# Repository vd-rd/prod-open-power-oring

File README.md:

# PowerPath controller with HotSwap protection

This module is designed to provide redundant power supply for power rails between 5-36V. Depending on the components that are populated on the board it can deliver up to 40A of current. The module can be used in a standalone configuration (switches are provided to select desired functionality) or can be controlled using the 2.54 pin header.

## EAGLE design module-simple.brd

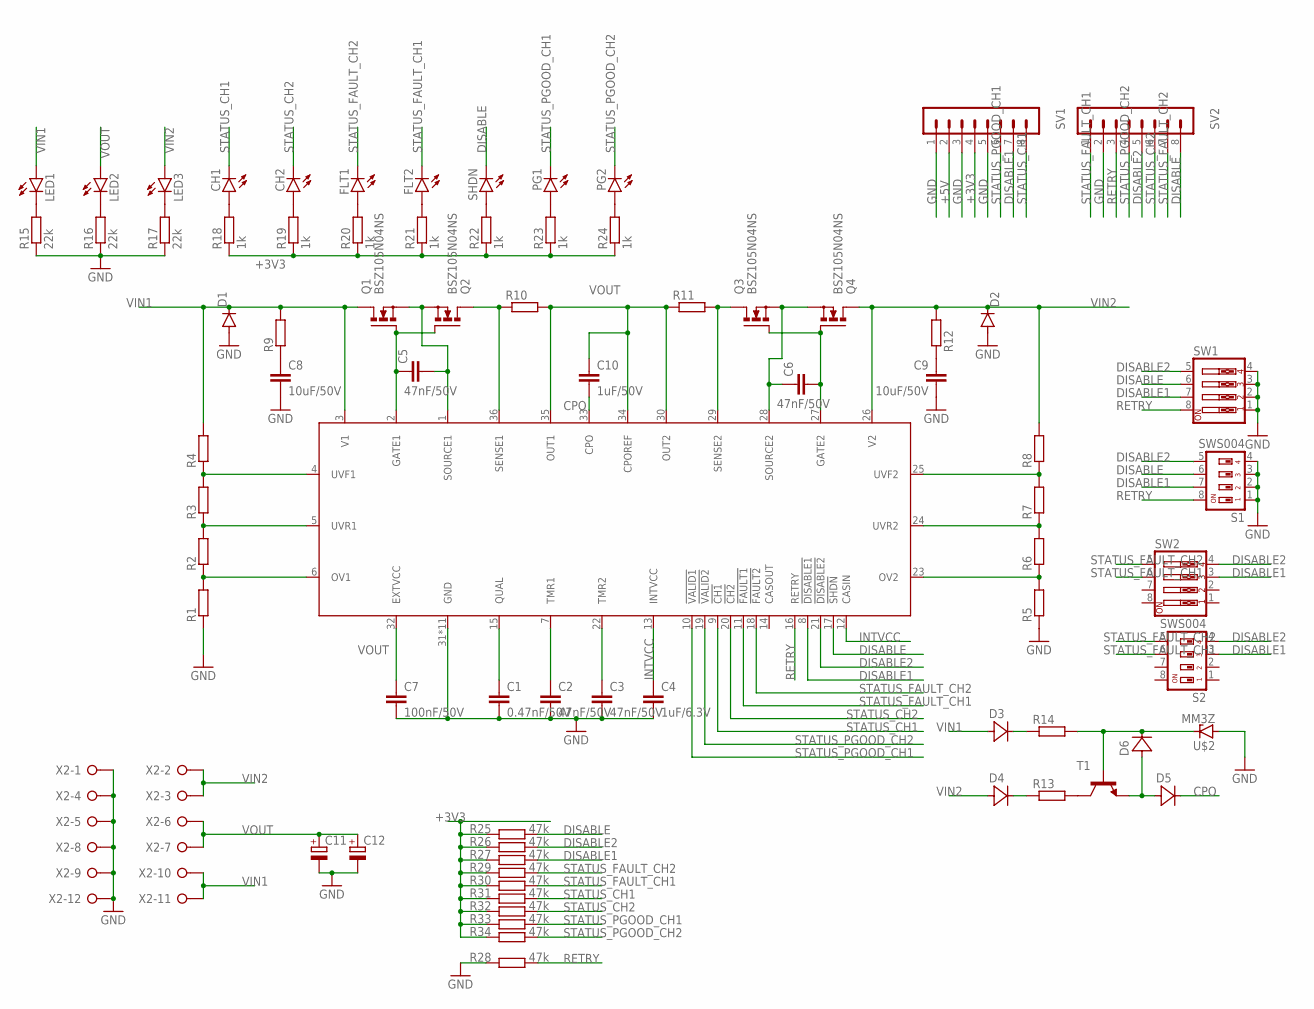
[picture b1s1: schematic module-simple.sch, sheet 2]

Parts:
C1: 0.47nF/50V; C0603
C2, C3, C5, C6: 47nF/50V; C0603
C4: 1uF/6.3V; C0603
C7: 100nF/50V; C0603
C8, C9: 10uF/50V; C1206
C10: 1uF/50V; C0805
C11, C12: CPOL-EU140CLH-1010; 140CLH-1010
CH1, CH2: LEDCHIP-LED0603; CHIP-LED0603
D1, D2: DIODE-DO214AC; DO214AC
D3, D4, D5, D6: 1N4148WS; SOD323
FLT1, FLT2: LEDCHIP-LED0603; CHIP-LED0603
LED1, LED2, LED3: LEDCHIP-LED0603; CHIP-LED0603
PG1, PG2: LEDCHIP-LED0603; CHIP-LED0603
Q1, Q2, Q3, Q4: BSZ105N04NS; PG-TDSON-8
R1, R2, R3, R4, R5, R6, R7, R8, R9, R12, R13, R14: R-EU_R0603; R0603
R10, R11: R-EU_R2512; R2512
R15, R16, R17: 22k; R0603
R18, R19, R20, R21, R22, R23, R24: 1k; R0603
R25, R26, R27, R28, R29, R30, R31, R32, R33, R34: 47k; R0603
S1, S2: SWS004; SMS-004
SHDN: LEDCHIP-LED0603; CHIP-LED0603
SV1, SV2: MA08-1
SW1, SW2: SW_DIP-4; EDG-04
T1: MMBT2222ALT1-NPN-SOT23-BEC; SOT23-BEC
U$1: LTC4421; QFN50P600X500X75-37T460X360N
U$2: MM3Z; SOD323
X2: W237-12P

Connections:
+3V3: R18.1, R19.1, R20.1, R21.1, R22.1, R23.1, R24.1, R25.1, R26.1, R27.1, R29.1, R30.1, R31.1, R32.1, R33.1, R34.1, SV1.4; also elsewhere on the board
+5V: SV1.2; also elsewhere on the board
CPO: C10.2, D5.K (C), U$1.33 (CPO)
DISABLE: R25.2, S1.6, SHDN.C, SV2.8, SW1.6, U$1.17 (!SHDN)
DISABLE1: R27.2, S1.7, S2.3, SV1.7, SW1.7, SW2.3, U$1.8 (!DISABLE1)
DISABLE2: R26.2, S1.5, S2.4, SV2.5, SW1.5, SW2.4, U$1.21 (!DISABLE2)
GND: C1.2, C2.2, C3.2, C4.2, C7.2, C8.2, C9.2, C11.-, C12.-, D1.A, D2.A, R1.1, R5.1, R15.1, R16.1, R17.1, R28.1, S1.1, S1.2, S1.3, S1.4, SV1.1, SV1.3, SV1.5, SV2.2, SW1.1, SW1.2, SW1.3, SW1.4, U$1.31 (GND), U$1.37 (GND), U$1.P$1 (GND), U$1.P$2 (GND), U$1.P$3 (GND), U$1.P$4 (GND), U$1.P$5 (GND), U$1.P$6 (GND), U$1.P$7 (GND), U$1.P$8 (GND), U$1.P$9 (GND), U$2.A, X2.1, X2.4, X2.5, X2.8, X2.9, X2.12; also elsewhere on the board
INTVCC: C4.1, U$1.12 (CASIN), U$1.13 (INTVCC)
unnamed: R1.2, R2.1, U$1.6 (OV1)
unnamed: R2.2, R3.1, U$1.5 (UVR1)
unnamed: R3.2, R4.1, U$1.4 (UVF1)
unnamed: R5.2, R6.1, U$1.23 (OV2)
unnamed: R6.2, R7.1, U$1.24 (UVR2)
unnamed: R7.2, R8.1, U$1.25 (UVF2)
unnamed: C5.1, Q1.4 (G), Q2.4 (G), U$1.2 (GATE1)
unnamed: C5.2, Q1.1 (S), Q1.2 (S), Q1.3 (S), Q2.1 (S), Q2.2 (S), Q2.3 (S), U$1.1 (SOURCE1)
unnamed: Q2.5 (D), Q2.6 (D), Q2.7 (D), Q2.8 (D), Q2.TH (D), R10.1, U$1.36 (SENSE1)
unnamed: C8.1, R9.1
unnamed: C9.1, R12.1
unnamed: D4.K (C), R13.1
unnamed: C1.1, U$1.15 (QUAL)
unnamed: Q3.5 (D), Q3.6 (D), Q3.7 (D), Q3.8 (D), Q3.TH (D), R11.2, U$1.29 (SENSE2)
unnamed: C6.2, Q3.4 (G), Q4.4 (G), U$1.27 (GATE2)
unnamed: C6.1, Q3.1 (S), Q3.2 (S), Q3.3 (S), Q4.1 (S), Q4.2 (S), Q4.3 (S), U$1.28 (SOURCE2)
unnamed: D3.K (C), R14.1
unnamed: C2.1, U$1.7 (TMR1)
unnamed: C3.1, U$1.22 (TMR2)
unnamed: R13.2, T1.C
unnamed: D6.K (C), R14.2, T1.B, U$2.K
unnamed: D5.A, D6.A, T1.E
unnamed: LED1.C, R15.2
unnamed: LED2.C, R16.2
unnamed: LED3.C, R17.2
unnamed: CH1.A, R18.2
unnamed: CH2.A, R19.2
unnamed: FLT1.A, R20.2
unnamed: FLT2.A, R21.2
unnamed: R22.2, SHDN.A
unnamed: PG1.A, R23.2
unnamed: PG2.A, R24.2
RETRY: R28.2, S1.8, SV2.3, SW1.8, U$1.16 (RETRY)
STATUS_CH1: CH1.C, R31.2, SV1.8, U$1.9 (!CH1)
STATUS_CH2: CH2.C, R32.2, SV2.6, U$1.20 (!CH2)
STATUS_FAULT_CH1: FLT2.C, R30.2, S2.6, SV2.1, SW2.6, U$1.11 (!FAULT1)
STATUS_FAULT_CH2: FLT1.C, R29.2, S2.5, SV2.7, SW2.5, U$1.18 (!FAULT2)
STATUS_PGOOD_CH1: PG1.C, R33.2, SV1.6, U$1.10 (!VALID1)
STATUS_PGOOD_CH2: PG2.C, R34.2, SV2.4, U$1.19 (!VALID2)
VIN1: D1.C, D3.A, LED1.A, Q1.5 (D), Q1.6 (D), Q1.7 (D), Q1.8 (D), Q1.TH (D), R4.2, R9.2, U$1.3 (V1), X2.10, X2.11
VIN2: D2.C, D4.A, LED3.A, Q4.5 (D), Q4.6 (D), Q4.7 (D), Q4.8 (D), Q4.TH (D), R8.2, R12.2, U$1.26 (V2), X2.2, X2.3
VOUT: C7.1, C10.1, C11.+, C12.+, LED2.A, R10.2, R11.1, U$1.30 (OUT2), U$1.32 (EXTVCC), U$1.34 (CPOREF), U$1.35 (OUT1), X2.6, X2.7; also elsewhere on the board

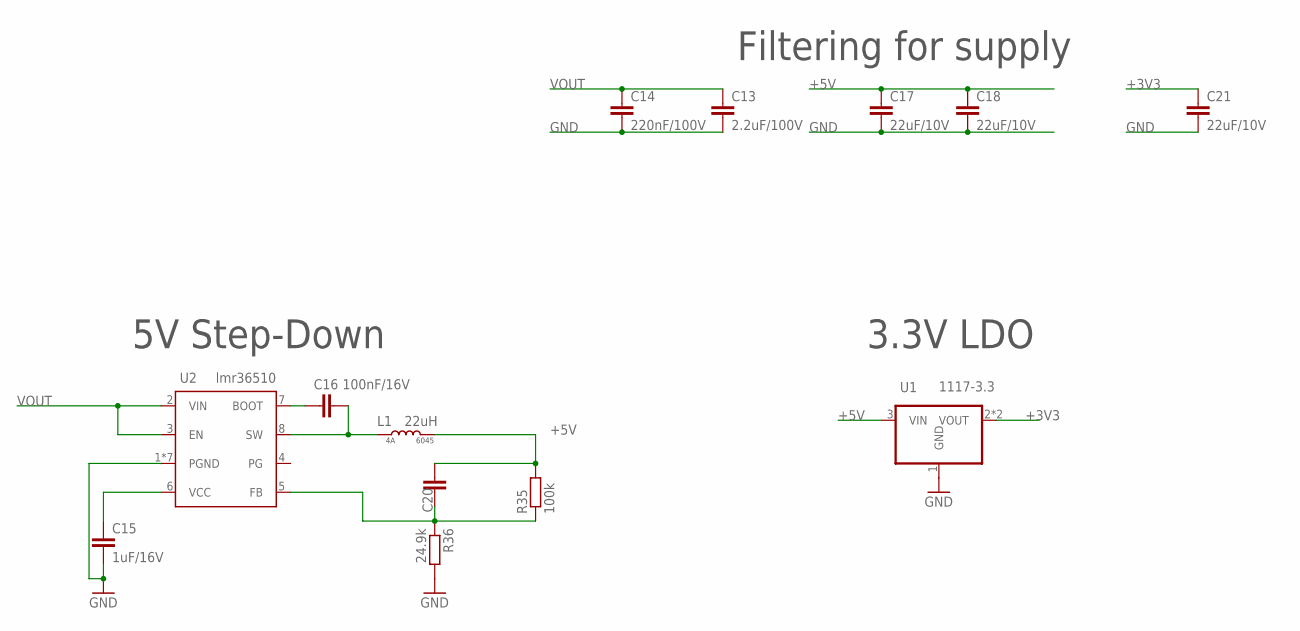
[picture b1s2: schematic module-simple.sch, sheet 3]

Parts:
C13: 2.2uF/100V; C1210
C14: 220nF/100V; C1210
C15: 1uF/16V; C0805
C16: 100nF/16V; C0805
C17, C18, C21: 22uF/10V; C1210
C20: C-EUC0603; C0603
L1: 22uH; DJNR6045
R35: 100k; R0603
R36: 24.9k; R0603
U1: 1117-3.3; SOT230P700X180-4
U2: lmr36510; SOIC127P600X170-9T240X310N

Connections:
+3V3: C21.1, U1.2 (VOUT), U1.4 (VOUT); also elsewhere on the board
+5V: C17.1, C18.1, C20.2, L1.P$2 (2), R35.2, U1.3 (VIN); also elsewhere on the board
GND: C13.2, C14.2, C15.2, C17.2, C18.2, C21.2, R36.2, U1.1 (GND), U2.1 (PGND), U2.9 (PGND), U2.P$1 (PGND), U2.P$2 (PGND), U2.P$3 (PGND), U2.P$4 (PGND), U2.P$5 (PGND); also elsewhere on the board
unnamed: C15.1, U2.6 (VCC)
unnamed: C16.1, U2.7 (BOOT)
unnamed: C16.2, L1.P$1 (1), U2.8 (SW)
unnamed: C20.1, R35.1, R36.1, U2.5 (FB)
VOUT: C13.1, C14.1, U2.2 (VIN), U2.3 (EN); also elsewhere on the board

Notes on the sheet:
5V Step-Down
3.3V LDO
Filtering for supply

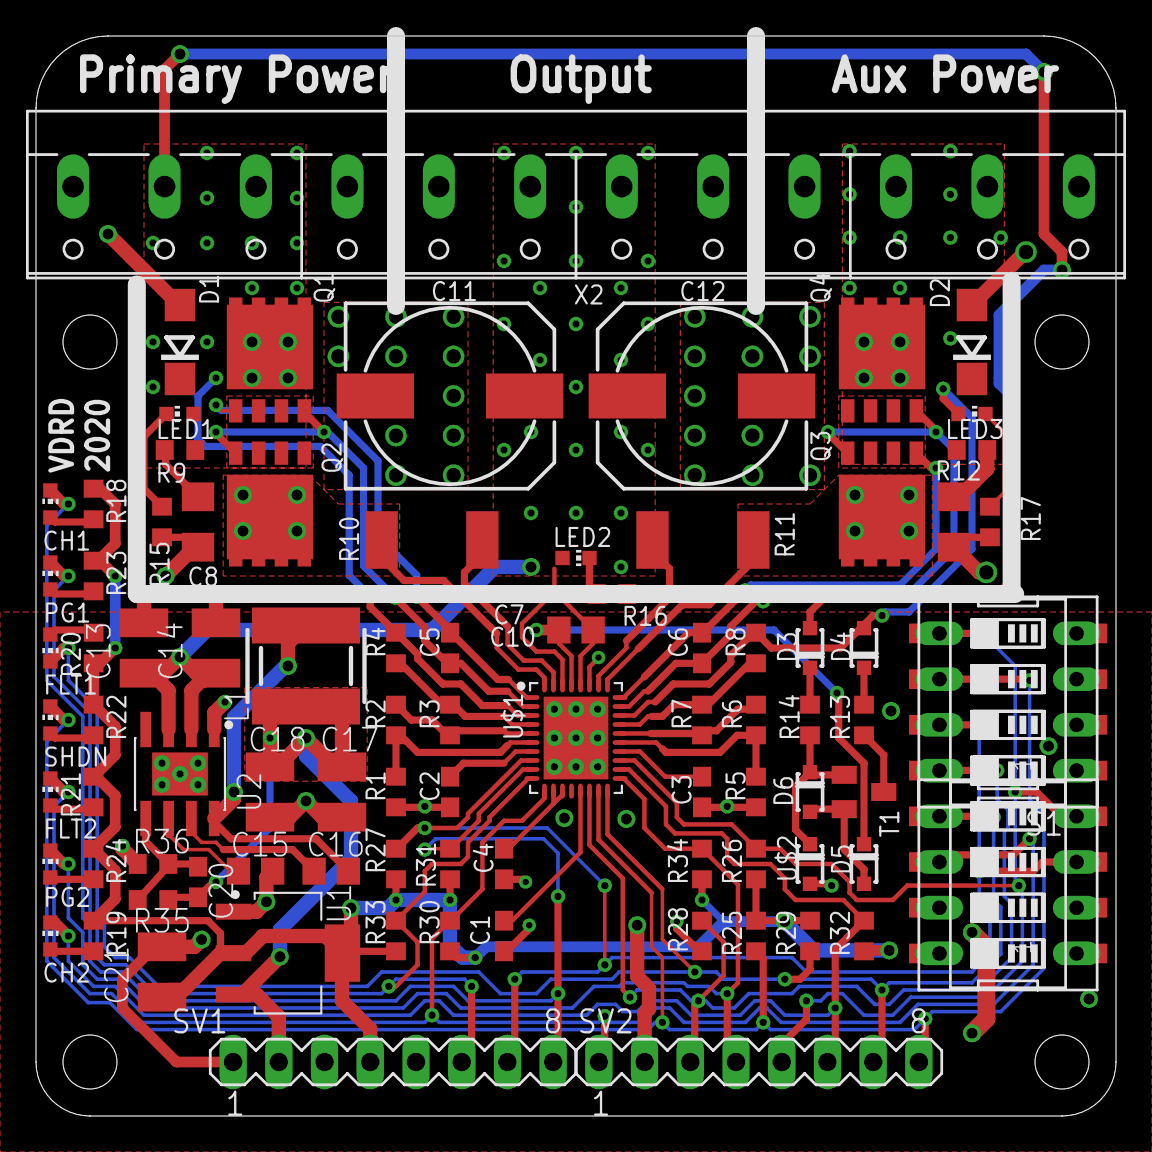
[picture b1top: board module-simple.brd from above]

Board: 2 copper layers, 60.0 x 60.0 mm, 89 parts (0 on the bottom side), 54 nets.

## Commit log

2020-11-21 project: initial floorplan
2020-11-21 project: define i/o
2020-11-22 project: add demoboard module
2020-11-23 project: finish features
2020-11-23 project: run drc and cosmetic fixes
2024-07-23 switched to kicad
2026-04-26 Refactor code structure for improved readability and maintainability
